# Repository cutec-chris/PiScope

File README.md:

# PiScope V3
PiScope is an small mobile Telescope for Astro and Nature Photography its designed to be as Mobile as Possible and can be driven with an Powerbank

The Step Resolution of the mechanic is:

Vertikal GradperStep:0.0703125<br>
Horizontal GradperStep:0.074800532<br>

## Lenses

[OH1](construction/OH1.md) - Lens holder for small C-Mount lenses like original raspberry Pi Lenses<br>
[OH2](construction/OH2.md) - Lens holder for Vivitar 70-200mm Cannon FD Tele Lens<br>
[OH3](construction/OH3.md) - Lens holder for Waveshare 8-50mm C-Mount Lens<br>
[OH4](construction/OH4.md) - Lens holder for Tokina 500mm FD Mount Lens<br>

## Electronics
The electronics consists of an [Raspberry Pi](https://www.raspberrypi.org/) and the [HAT PCB](electronic/HAT/README.md) wich contains Motor Drivers, and Compass

## Prices

Position           | Quantity | Price | Full
------------------ | -------- | ---- | -----
3D printed Parts | 1 | ~5$ | 5$
Raspberry Pi 3 | 1 | ~ 35$ | 35$
28BYJ-48 | 2 | ~3$ | 6$
Bearing 13mm | 2 | 0.4$ | 0.8$
Raspberry Pi HQ Camera | 1 | 53$ | 53$
[HAT PCB](electronic/HAT/README.md#BOM) | 1 | 6.5$ | 6.5$
| | | | 106.3$

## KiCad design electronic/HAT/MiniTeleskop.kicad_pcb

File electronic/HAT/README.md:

This is an Motor Driver Board created for the [PiScope](https://github.com/cutec-chris/PiScope). 

It contains:
* 4 Motor Drivers wich can be used with ULN2003 or alternte DRV8825. The ULN2003 can be used with 28BYJ-48 and DEV8825 with NEMAxx<br> 
* Compass Module suppport for HMC5883L:<br>
* 4 Endswitches: <br>

## BOM

Position           | Quantity | Price | Full
------------------ | -------- | ---- | -----
PCB | 1 | ~3$ | 3$
ULN2003A | 3 | ~ 0.3$ | 0.9$
JST Pinheader | 3 | ~0.2$ | 0.6$
PI Header | 1 | ~2$ | 2$
| | | | 6.5$

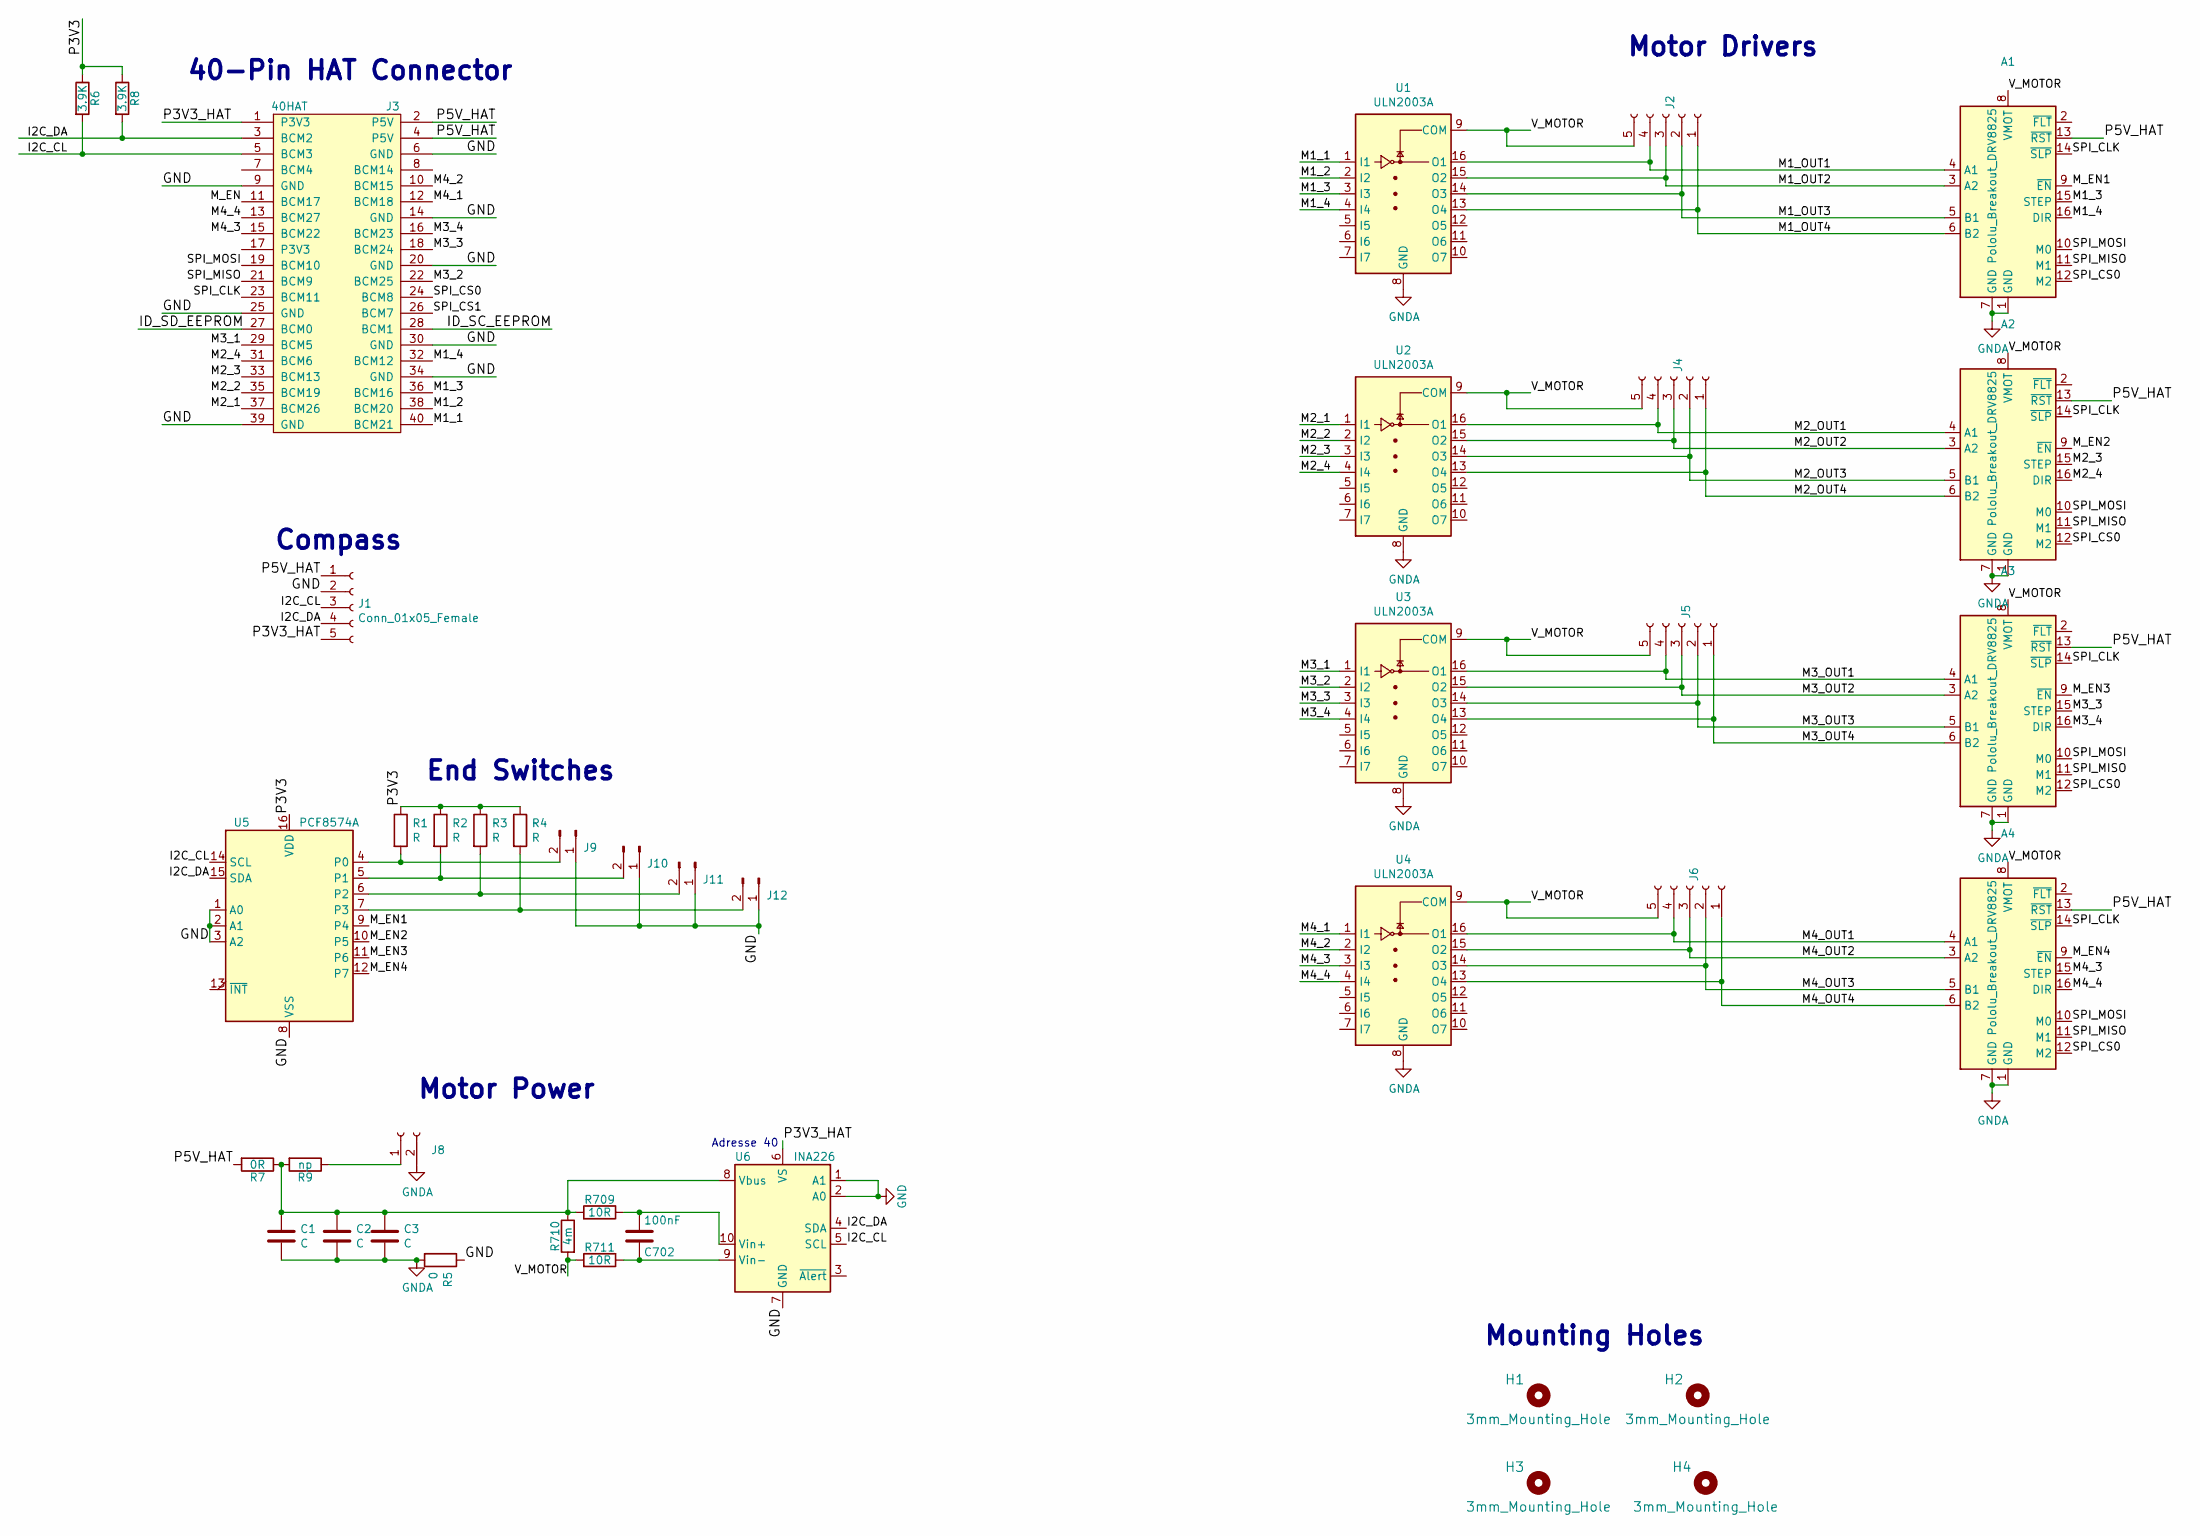
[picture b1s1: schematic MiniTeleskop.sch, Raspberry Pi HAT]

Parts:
A1, A2, A3, A4: Pololu_Breakout_DRV8825; Pololu_Breakout-16_15.2x20.3mm
C1, C2, C3: C; C_1206_3216Metric_Pad1.42x1.75mm_HandSolder
C702: 100nF; C_0805_2012Metric
H1, H2, H3, H4: 3mm_Mounting_Hole; NPTH_3mm_ID
J1: Conn_01x05_Female; PinHeader_1x05_P2.54mm_Vertical
J2, J4, J5, J6: Conn_01x05_Female; JST_XH_B5B-XH-A_1x05_P2.50mm_Vertical
J3: 40HAT; PinSocket_2x20_P2.54mm_Vertical
J8: Conn_01x02_Female; JST_NV_B02P-NV_1x02_P5.00mm_Vertical
J9, J10, J11, J12: Conn_01x02_Male; PinHeader_1x02_P2.54mm_Vertical
R1, R2, R3, R4: R; R_0805_2012Metric_Pad1.15x1.40mm_HandSolder
R5: 0; R_0805_2012Metric_Pad1.15x1.40mm_HandSolder
R6, R8: 3.9K; R_0805_2012Metric_Pad1.15x1.40mm_HandSolder
R7: 0R; R_0805_2012Metric_Pad1.15x1.40mm_HandSolder
R9: np; R_0805_2012Metric_Pad1.15x1.40mm_HandSolder
R709, R711: 10R; R_0805_2012Metric
R710: 4m; R_2512_6332Metric
U1, U2, U3, U4: ULN2003A; SOIC-16_3.9x9.9mm_P1.27mm
U5: PCF8574A; SOIC-16W_7.5x10.3mm_P1.27mm
U6: INA226; VSSOP-10_3x3mm_P0.5mm

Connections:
/I2C_CL: J1.3, J3.5 (BCM3), R6.2, U5.14 (SCL), U6.5 (SCL)
/I2C_DA: J1.4, J3.3 (BCM2), R8.2, U5.15 (SDA), U6.4 (SDA)
/ID_SC_EEPROM: J3.28 (BCM1)
/ID_SD_EEPROM: J3.27 (BCM0)
/M1_1: J3.40 (BCM21), U1.1 (I1)
/M1_2: J3.38 (BCM20), U1.2 (I2)
/M1_3: A1.15 (STEP), J3.36 (BCM16), U1.3 (I3)
/M1_4: A1.16 (DIR), J3.32 (BCM12), U1.4 (I4)
/M1_OUT1: A1.4 (A1), J2.4, U1.16 (O1)
/M1_OUT2: A1.3 (A2), J2.3, U1.15 (O2)
/M1_OUT3: A1.5 (B1), J2.2, U1.14 (O3)
/M1_OUT4: A1.6 (B2), J2.1, U1.13 (O4)
/M2_1: J3.37 (BCM26), U2.1 (I1)
/M2_2: J3.35 (BCM19), U2.2 (I2)
/M2_3: A2.15 (STEP), J3.33 (BCM13), U2.3 (I3)
/M2_4: A2.16 (DIR), J3.31 (BCM6), U2.4 (I4)
/M2_OUT1: A2.4 (A1), J4.4, U2.16 (O1)
/M2_OUT2: A2.3 (A2), J4.3, U2.15 (O2)
/M2_OUT3: A2.5 (B1), J4.2, U2.14 (O3)
/M2_OUT4: A2.6 (B2), J4.1, U2.13 (O4)
/M3_1: J3.29 (BCM5), U3.1 (I1)
/M3_2: J3.22 (BCM25), U3.2 (I2)
/M3_3: A3.15 (STEP), J3.18 (BCM24), U3.3 (I3)
/M3_4: A3.16 (DIR), J3.16 (BCM23), U3.4 (I4)
/M3_OUT1: A3.4 (A1), J5.4, U3.16 (O1)
/M3_OUT2: A3.3 (A2), J5.3, U3.15 (O2)
/M3_OUT3: A3.5 (B1), J5.2, U3.14 (O3)
/M3_OUT4: A3.6 (B2), J5.1, U3.13 (O4)
/M4_1: J3.12 (BCM18), U4.1 (I1)
/M4_2: J3.10 (BCM15), U4.2 (I2)
/M4_3: A4.15 (STEP), J3.15 (BCM22), U4.3 (I3)
/M4_4: A4.16 (DIR), J3.13 (BCM27), U4.4 (I4)
/M4_OUT1: A4.4 (A1), J6.4, U4.16 (O1)
/M4_OUT2: A4.3 (A2), J6.3, U4.15 (O2)
/M4_OUT3: A4.5 (B1), J6.2, U4.14 (O3)
/M4_OUT4: A4.6 (B2), J6.1, U4.13 (O4)
/M_EN: J3.11 (BCM17)
/M_EN1: A1.9 (~EN), U5.9 (P4)
/M_EN2: A2.9 (~EN), U5.10 (P5)
/M_EN3: A3.9 (~EN), U5.11 (P6)
/M_EN4: A4.9 (~EN), U5.12 (P7)
/P3V3: R1.1, R2.1, R3.1, R4.1, R6.1, R8.1, U5.16 (VDD)
/P3V3_HAT: J1.5, J3.1 (P3V3), U6.6 (VS)
/P5V_HAT: A1.13 (~RST), A2.13 (~RST), A3.13 (~RST), A4.13 (~RST), J1.1, J3.2 (P5V), J3.4 (P5V), R7.2
/SPI_CLK: A1.14 (~SLP), A2.14 (~SLP), A3.14 (~SLP), A4.14 (~SLP), J3.23 (BCM11)
/SPI_CS0: A1.12 (M2), A2.12 (M2), A3.12 (M2), A4.12 (M2), J3.24 (BCM8)
/SPI_CS1: J3.26 (BCM7)
/SPI_MISO: A1.11 (M1), A2.11 (M1), A3.11 (M1), A4.11 (M1), J3.21 (BCM9)
/SPI_MOSI: A1.10 (M0), A2.10 (M0), A3.10 (M0), A4.10 (M0), J3.19 (BCM10)
/V_MOTOR: A1.8 (VMOT), A2.8 (VMOT), A3.8 (VMOT), A4.8 (VMOT), J2.5, J4.5, J5.5, J6.5, R710.2, R711.2, U1.9 (COM), U2.9 (COM), U3.9 (COM), U4.9 (COM)
GND: J1.2, J3.6 (GND), J3.9 (GND), J3.14 (GND), J3.20 (GND), J3.25 (GND), J3.30 (GND), J3.34 (GND), J3.39 (GND), J9.1, J10.1, J11.1, J12.1, R5.1, U5.1 (A0), U5.2 (A1), U5.3 (A2), U5.8 (VSS), U6.1 (A1), U6.2 (A0), U6.7 (GND)
GNDA: A1.1 (GND), A1.7 (GND), A2.1 (GND), A2.7 (GND), A3.1 (GND), A3.7 (GND), A4.1 (GND), A4.7 (GND), C1.2, C2.2, C3.2, J8.2, R5.2, U1.8 (GND), U2.8 (GND), U3.8 (GND), U4.8 (GND)
unnamed: C1.1, C2.1, C3.1, R7.1, R9.2, R709.2, R710.1, U6.8 (Vbus)
unnamed: C702.1, R711.1, U6.9 (Vin-)
unnamed: C702.2, R709.1, U6.10 (Vin+)
unnamed: J8.1, R9.1
unnamed: J9.2, R1.2, U5.4 (P0)
unnamed: J10.2, R2.2, U5.5 (P1)
unnamed: J11.2, R3.2, U5.6 (P2)
unnamed: J12.2, R4.2, U5.7 (P3)

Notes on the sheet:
Mounting Holes
40-Pin HAT Connector
Adresse 40
Motor Power
Motor Drivers
End Switches
Compass

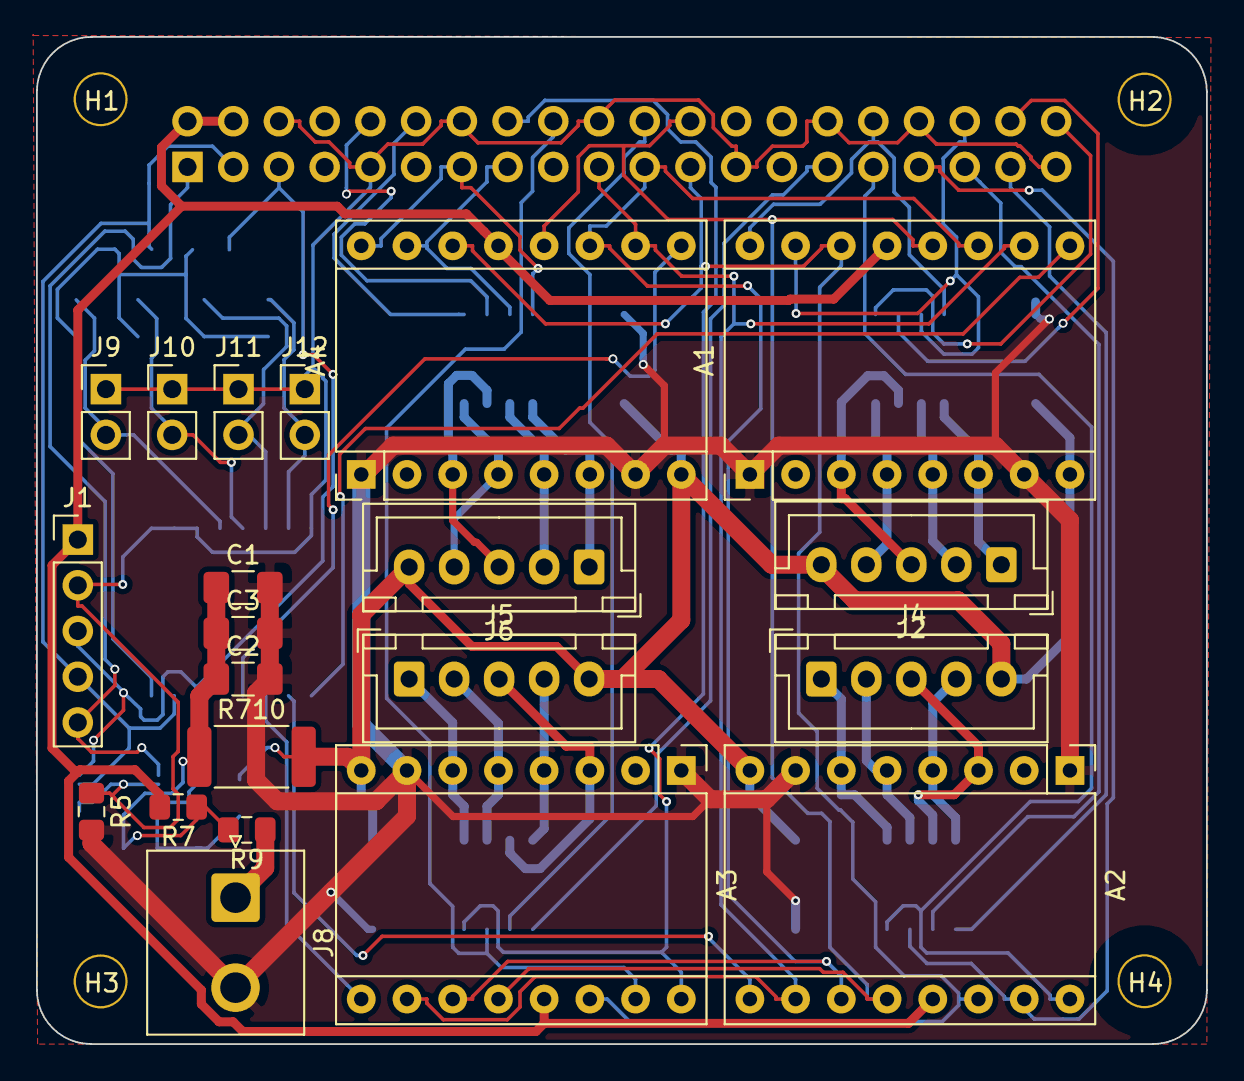
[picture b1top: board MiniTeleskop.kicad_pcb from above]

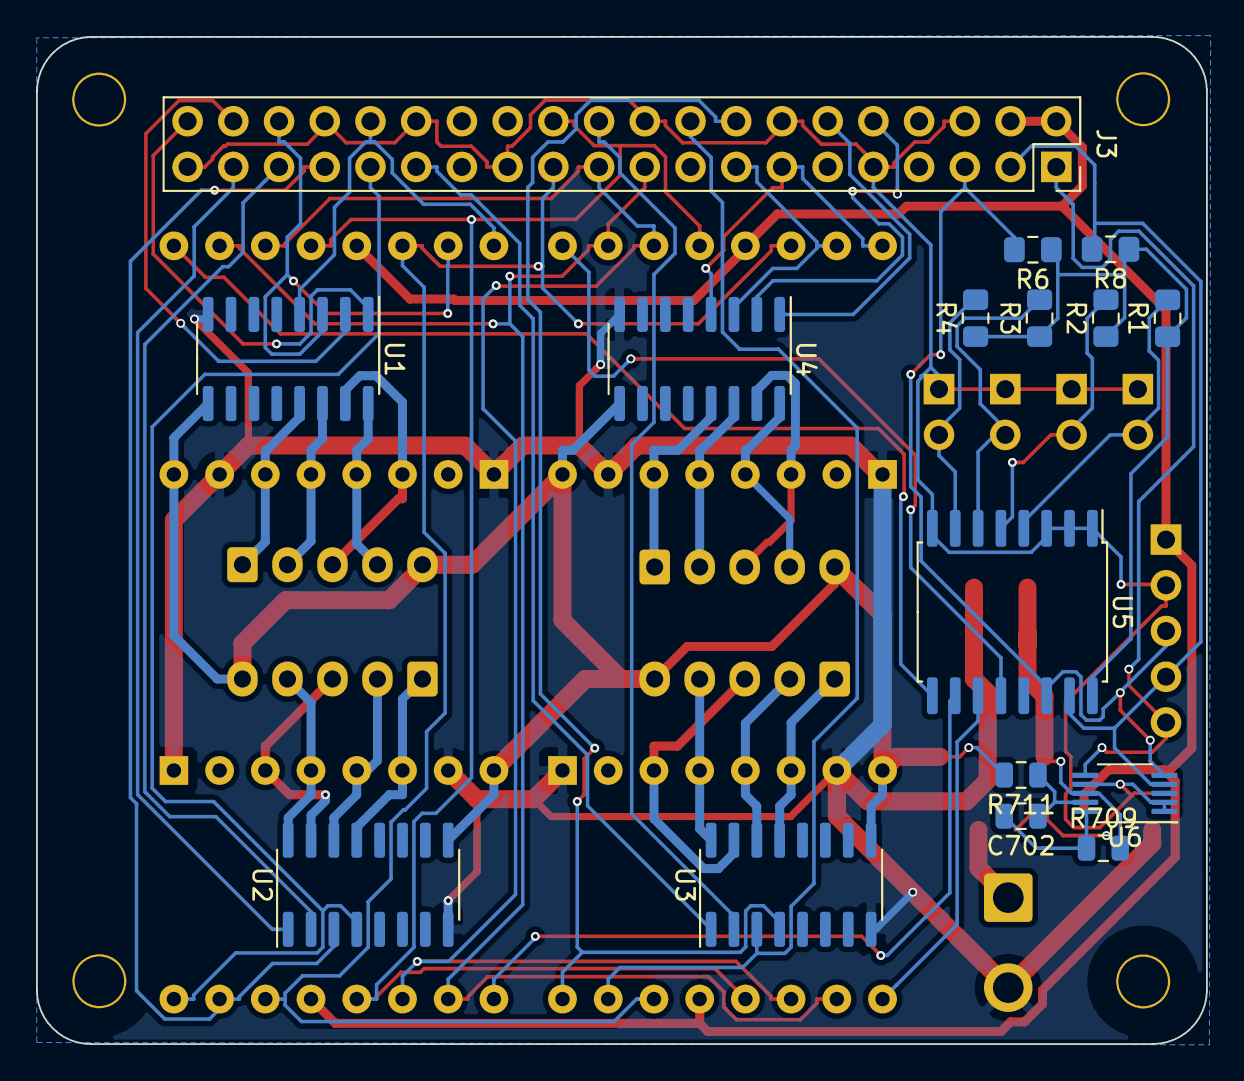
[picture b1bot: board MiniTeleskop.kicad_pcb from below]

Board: 2 copper layers, 65.0 x 56.0 mm, 41 parts (16 on the bottom side), 56 nets.

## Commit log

2020-10-03 Initial Move from private Repo
2020-10-03 better transparency
2020-10-03 Add Tokina 500mm lensholder
2020-10-03 Add missing file
2020-10-03 First Useable Version of Tokina Holder?
2020-10-03 Add documentation for Electronics
2020-10-03 BOMs
2020-10-08 Add USB Camera
2020-10-08 Add USB camera to Base
